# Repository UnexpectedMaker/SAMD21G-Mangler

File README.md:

# SAMD21G-Mangler
SAMD21G Mangler Design Files

Inlcluded in this reposity:
- EagleCAD schematics and Board layout files (Eagle 9.1) 
- Exported Gerber files (Gerber 274X)
- STL files for the base, chip holder and base brackets

Enjoy!

# Support me? 
I love making and designing projects but sharing open source projects takes a lot of thought and time. I do it because I think it’s important to share knowledge and give back to the community like many have done before me.

If you find this project useful or want to see more open source projects like it, please consider buying one of my products at

https://unexpectedmaker.com/shop

or

https://www.tindie.com/stores/seonr/

of by backing me on Patreon to say thanks!

# Unexpected Maker
http://youtube.com/c/unexpectedmaker

http://twitter.com/unexpectedmaker

https://www.facebook.com/unexpectedmaker/

https://www.instagram.com/unexpectedmaker/

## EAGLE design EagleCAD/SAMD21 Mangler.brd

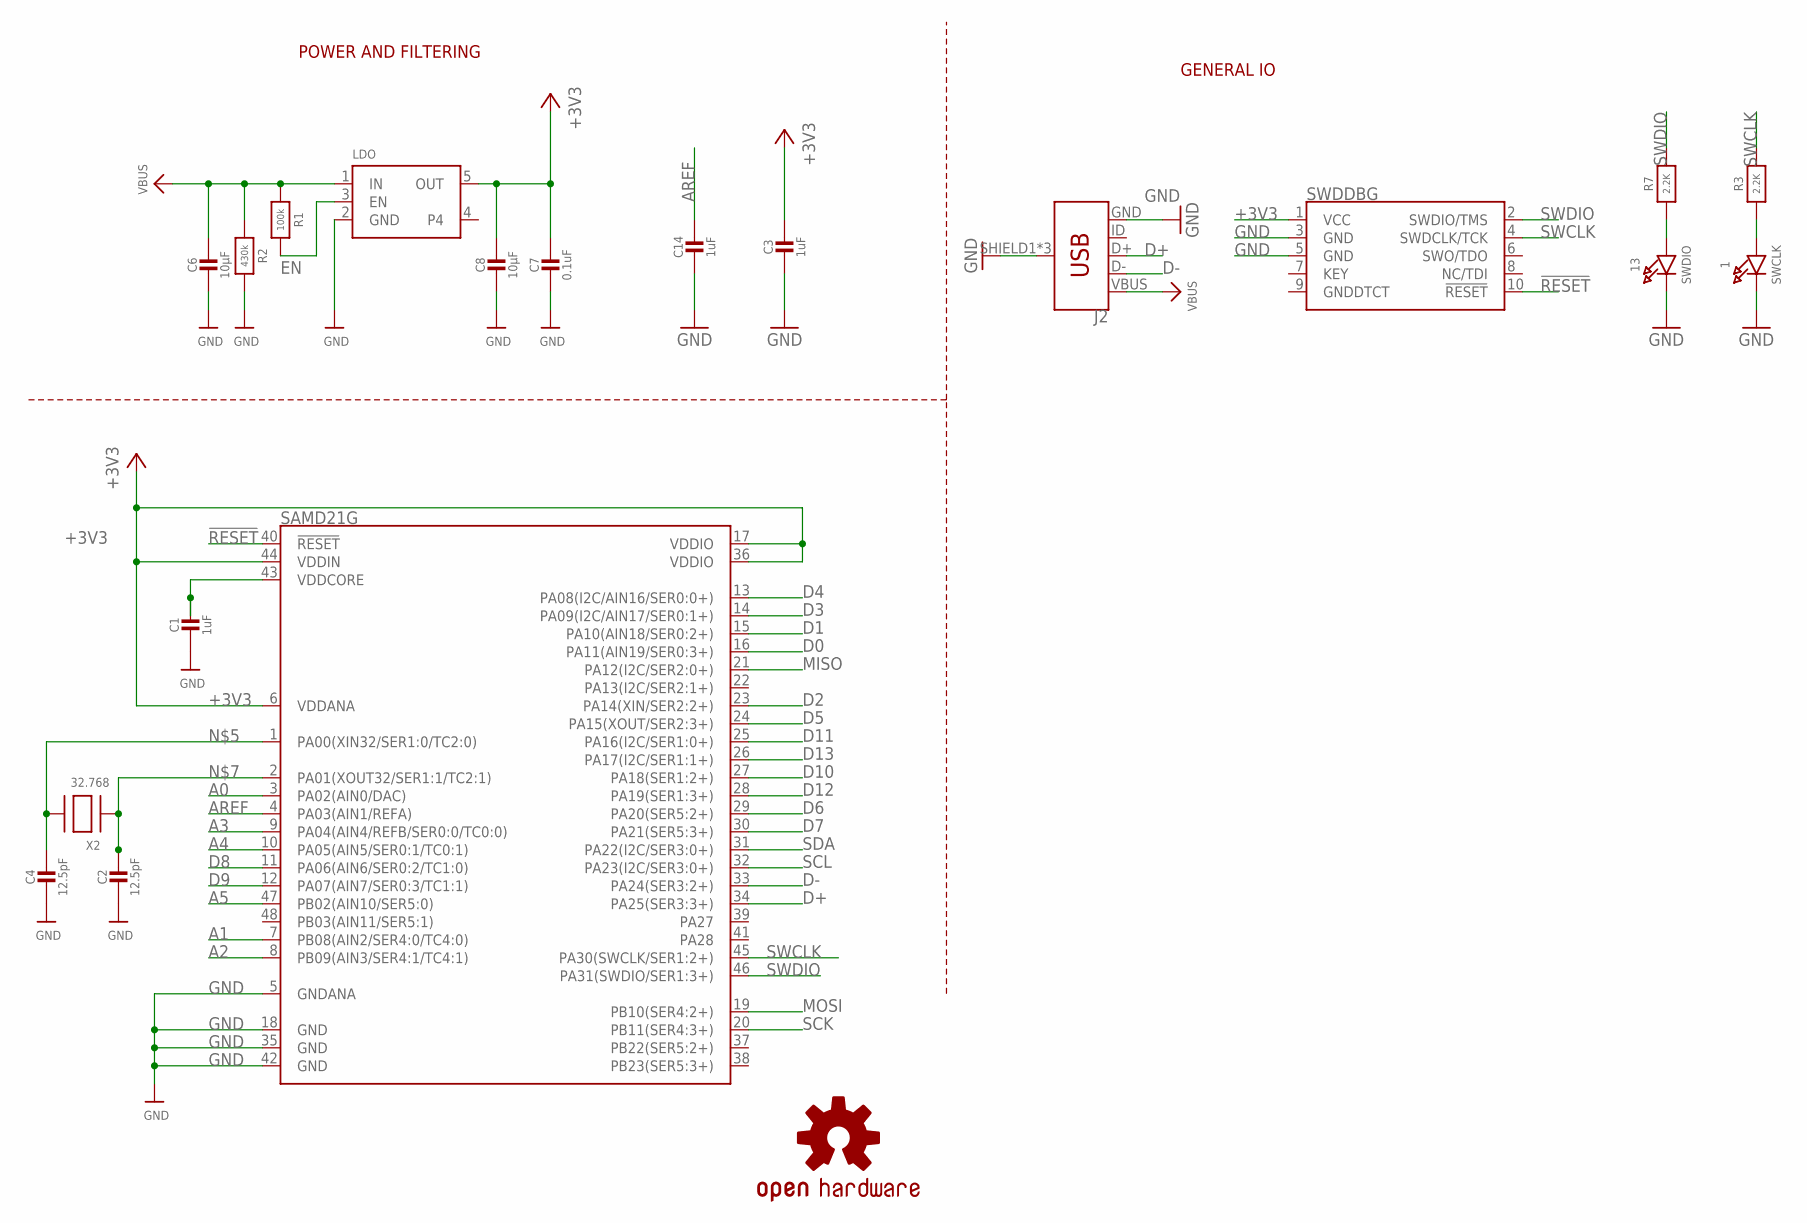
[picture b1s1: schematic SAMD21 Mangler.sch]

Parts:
1: SWCLK; CHIPLED_0805_NOOUTLINE
13: SWDIO; CHIPLED_0805_NOOUTLINE
C1, C3, C14: 1uF; 0805-NO
C2, C4: 12.5pF; 0805-NO
C6, C8: 10µF; 0805-NO
C7: 0.1uF; 0805-NO
J2: USB_MICRO-BREDUCED_PASTE; USB-B-MICRO-SMD_RED_PASTE
LDO: VREG_SOT23-5; SOT23-5
LOGO1: OSHW-LOGOS; OSHW-LOGO-S
R1: 100k; 0805-NO
R2: 430k; 0805-NO
R3, R7: 2.2K; 0805-NO
SAMD21G: ATSAMD21G-A; TQFP-48
SWDDBG: CORTEX_DEBUG_PTH; 2X5-PTH-1.27MM
X2: 32.768; XTAL3215

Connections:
!RESET: SAMD21G.40 (!RESET!), SWDDBG.10 (!RESET)
+3V3: C3.1, C7.1, C8.1, LDO.5 (OUT), SAMD21G.6 (VDDANA), SAMD21G.17 (VDDIO), SAMD21G.36 (VDDIO), SAMD21G.44 (VDDIN), SWDDBG.1 (VCC)
A0: SAMD21G.3 (PA02(AIN0/DAC))
A1: SAMD21G.7 (PB08(AIN2/SER4:0/TC4:0))
A2: SAMD21G.8 (PB09(AIN3/SER4:1/TC4:1))
A3: SAMD21G.9 (PA04(AIN4/REFB/SER0:0/TC0:0))
A4: SAMD21G.10 (PA05(AIN5/SER0:1/TC0:1))
A5: SAMD21G.47 (PB02(AIN10/SER5:0))
AREF: C14.1, SAMD21G.4 (PA03(AIN1/REFA))
D0: SAMD21G.16 (PA11(AIN19/SER0:3+))
D1: SAMD21G.15 (PA10(AIN18/SER0:2+))
D2: SAMD21G.23 (PA14(XIN/SER2:2+))
D3: SAMD21G.14 (PA09(I2C/AIN17/SER0:1+))
D4: SAMD21G.13 (PA08(I2C/AIN16/SER0:0+))
D5: SAMD21G.24 (PA15(XOUT/SER2:3+))
D6: SAMD21G.29 (PA20(SER5:2+))
D7: SAMD21G.30 (PA21(SER5:3+))
D8: SAMD21G.11 (PA06(AIN6/SER0:2/TC1:0))
D9: SAMD21G.12 (PA07(AIN7/SER0:3/TC1:1))
D10: SAMD21G.27 (PA18(SER1:2+))
D11: SAMD21G.25 (PA16(I2C/SER1:0+))
D12: SAMD21G.28 (PA19(SER1:3+))
D13: SAMD21G.26 (PA17(I2C/SER1:1+))
D+: J2.D+, SAMD21G.34 (PA25(SER3:3+))
D-: J2.D-, SAMD21G.33 (PA24(SER3:2+))
EN: LDO.3 (EN), R1.2
GND: 1.C, 13.C, C1.2, C2.2, C3.2, C4.2, C6.2, C7.2, C8.2, C14.2, J2.GND, J2.SHIELD1 (SHIELD), J2.SHIELD2 (SHIELD), J2.SHIELD3 (SHIELD), LDO.2 (GND), R2.2, SAMD21G.5 (GNDANA), SAMD21G.18 (GND), SAMD21G.35 (GND), SAMD21G.42 (GND), SWDDBG.3 (GND), SWDDBG.5 (GND)
MISO: SAMD21G.21 (PA12(I2C/SER2:0+))
MOSI: SAMD21G.19 (PB10(SER4:2+))
unnamed: 1.A, R3.2
unnamed: 13.A, R7.2
unnamed: C4.1, SAMD21G.1 (PA00(XIN32/SER1:0/TC2:0)), X2.P$2
unnamed: C2.1, SAMD21G.2 (PA01(XOUT32/SER1:1/TC2:1)), X2.P$1
SCK: SAMD21G.20 (PB11(SER4:3+))
SCL: SAMD21G.32 (PA23(I2C/SER3:0+))
SDA: SAMD21G.31 (PA22(I2C/SER3:0+))
SWCLK: R3.1, SAMD21G.45 (PA30(SWCLK/SER1:2+)), SWDDBG.4 (SWDCLK/TCK)
SWDIO: R7.1, SAMD21G.46 (PA31(SWDIO/SER1:3+)), SWDDBG.2 (SWDIO/TMS)
VBUS: C6.1, J2.VBUS, LDO.1 (IN), R1.1, R2.1
VDDCORE: C1.1, SAMD21G.43 (VDDCORE)

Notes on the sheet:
POWER AND FILTERING
GENERAL IO

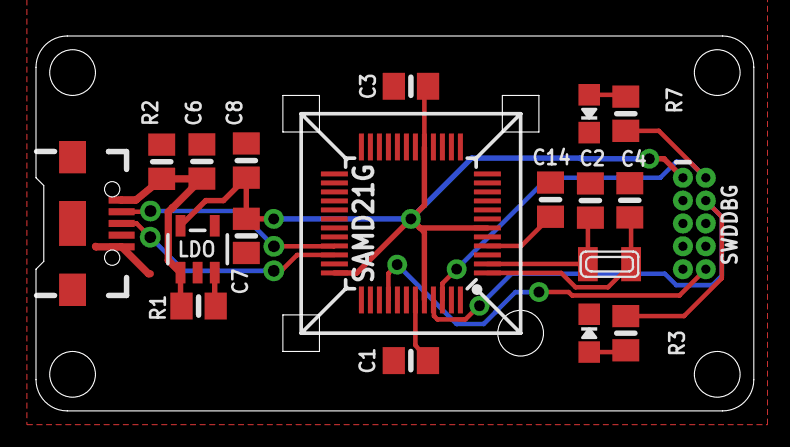
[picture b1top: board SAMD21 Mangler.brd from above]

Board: 2 copper layers, 39.9 x 20.8 mm, 20 parts (1 on the bottom side), 15 nets.

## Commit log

2018-07-03 Initial commit of desiogn files for rev 2018-2
2018-07-03 Up[dated Readme
2018-07-26 Update README.md
    Added donate button
2020-10-02 Updated readme and license

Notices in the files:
parts and their libraries:
microbuilder: This work is placed in the public domain, and may be freely used for commercial and non-commercial work with the following conditions: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
SparkFun-IC-Microcontroller: Licensing: Creative Commons ShareAlike 4.0 International - https://creativecommons.org/licenses/by-sa/4.0
